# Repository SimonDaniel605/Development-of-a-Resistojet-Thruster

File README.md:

# Development of a Resistojet Thruster
This repository contains the design, modelling, simulation, and development of a low-power electrothermal resistojet propulsion system for nanosatellite station-keeping and orbital manoeuvring.

The project forms part of an MEng (Electronic Engineering) research project at Stellenbosch University and focuses on developing a compact, efficient, and manufacturable propulsion system capable of providing precise orbital manoeuvring for future small satellite missions.

The work includes analytical modelling, CFD validation, hardware development, electronics, embedded software, and experimental test infrastructure.

## Author
**Simon Daniel**  
MEng Candidate  
Electronic Systems Laboratory (ESL)  
Department of Electrical and Electronic Engineering  
Stellenbosch University

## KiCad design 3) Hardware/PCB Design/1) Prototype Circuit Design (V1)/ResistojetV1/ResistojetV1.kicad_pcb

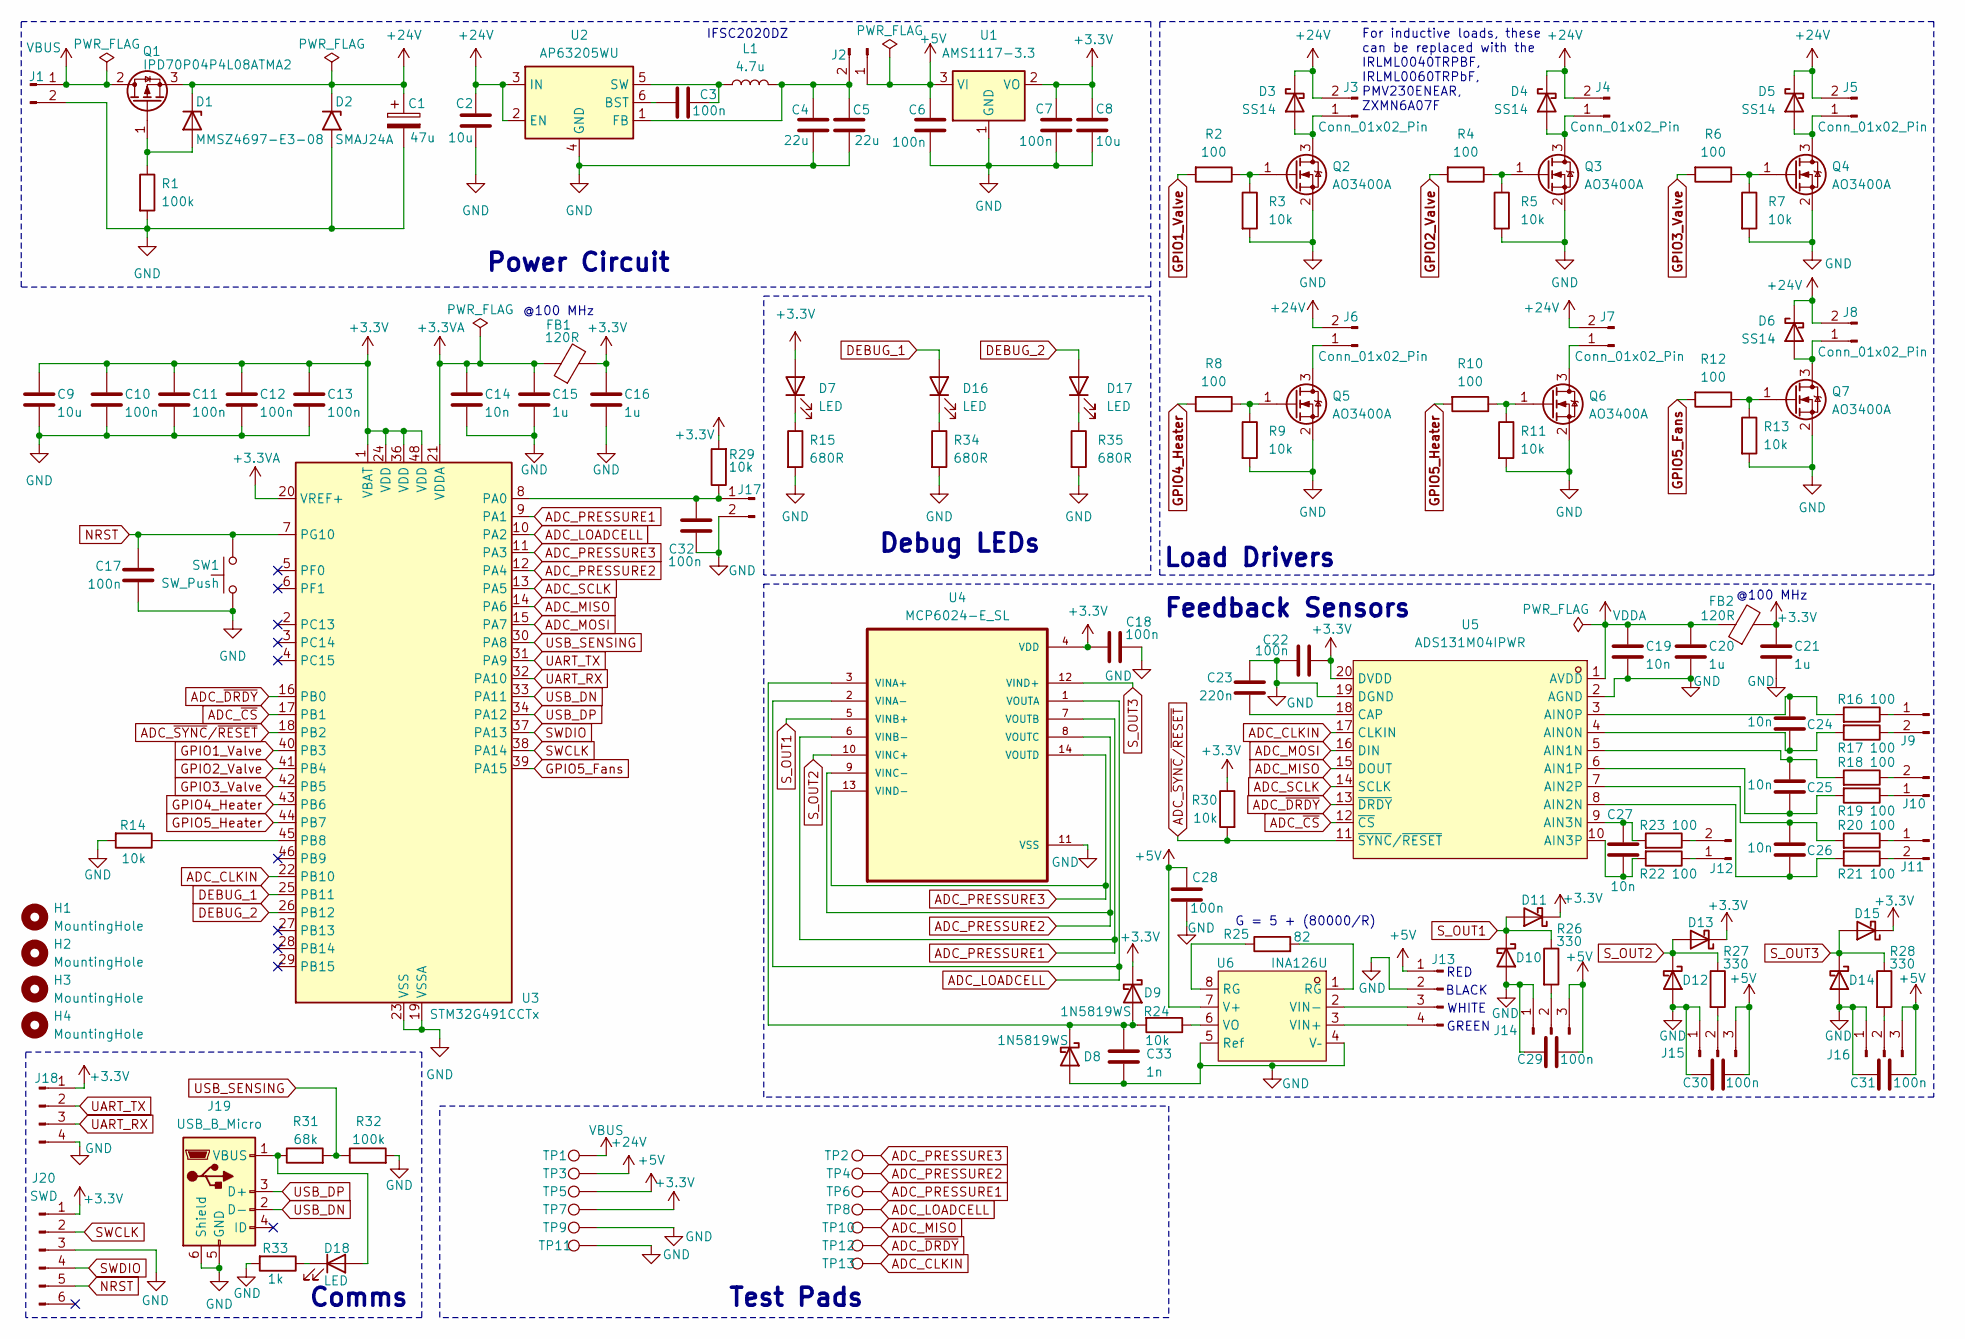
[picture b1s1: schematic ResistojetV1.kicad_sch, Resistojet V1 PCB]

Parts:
C1: 47u; CP_Elec_6.3x7.7
C2, C8, C9: 10u; C_0805_2012Metric
C3, C6, C7: 100n; C_0603_1608Metric
C4, C5: 22u; C_0805_2012Metric
C10, C11, C12, C13, C17, C18, C22, C28, C29, C30, C31, C32: 100n; C_0402_1005Metric
C14, C19, C24, C25, C26, C27: 10n; C_0402_1005Metric
C15, C16, C20, C21: 1u; C_0603_1608Metric
C23: 220n; C_0603_1608Metric
C33: 1n; C_0603_1608Metric
D1: MMSZ4697-E3-08; D_SOD-123
D2: SMAJ24A; D_SMA
D3, D4, D5, D6: SS14; D_SMA
D7, D16, D17, D18: LED; LED_0603_1608Metric
D8, D9, D10, D11, D12, D13, D14, D15: 1N5819WS; D_SOD-323
FB1, FB2: 120R; L_0603_1608Metric
H1, H2, H3, H4: MountingHole; MountingHole_3.2mm_M3
J1, J6, J7: Conn_01x02_Pin; JST_VH_B2P-VH_1x02_P3.96mm_Vertical
J2: Conn_01x02_Pin; PinHeader_1x02_P2.54mm_Vertical
J3, J4, J5, J8, J9, J10, J11, J12, J17: Conn_01x02_Pin; JST_PH_B2B-PH-K_1x02_P2.00mm_Vertical
J13, J18: Conn_01x04_Pin; JST_PH_B4B-PH-K_1x04_P2.00mm_Vertical
J14, J15, J16: Conn_01x03_Pin; JST_PH_B3B-PH-K_1x03_P2.00mm_Vertical
J19: USB_B_Micro; USB_Micro-B_Molex-105017-0001
J20: SWD; JST_PH_B6B-PH-K_1x06_P2.00mm_Vertical
L1: 4.7u; L_APV_ANR5040
Q1: IPD70P04P4L08ATMA2; TO-252-3_TabPin2
Q2, Q3, Q4, Q5, Q6, Q7: AO3400A; SOT-23
R1, R32: 100k; R_0603_1608Metric
R2, R4, R6, R8, R10, R12, R16, R17, R18, R19, R20, R21, R22, R23: 100; R_0603_1608Metric
R3, R5, R7, R9, R11, R13, R14, R24, R29, R30: 10k; R_0603_1608Metric
R15, R34, R35: 680R; R_0603_1608Metric
R25: 82; R_0603_1608Metric
R26, R27, R28: 330; R_0603_1608Metric
R31: 68k; R_0603_1608Metric
R33: 1k; R_0603_1608Metric
SW1: SW_Push; SW-SMD_L3.9-W3.0-P4.45
TP1, TP2, TP3, TP4, TP5, TP6, TP7, TP8, TP9, TP10, TP11, TP12, TP13: TestPoint; TestPoint_Pad_D1.0mm
U1: AMS1117-3.3; SOT-223-3_TabPin2
U2: AP63205WU; TSOT-23-6
U3: STM32G491CCTx; LQFP-48_7x7mm_P0.5mm
U4: MCP6024-E_SL; SOIC127P600X175-14N
U5: ADS131M04IPWR; TSSOP-20_L6.5-W4.4-P0.65-LS6.4-BL; MPN ADS131M04IPWR; LCSC Part C2862562
U6: INA126U; SOIC-8_L4.9-W3.9-P1.27-LS6.0-BL; MPN INA126U; LCSC Part C1346079

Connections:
+3.3V: C7.2, C8.2, C9.1, C10.1, C11.1, C12.1, C13.1, C16.1, C18.1, C21.1, C22.2, D7.2 (A), D9.1 (K), D11.1 (K), D13.1 (K), D15.1 (K), FB1.2, FB2.2, J18.1, J20.1, R29.2, R30.1, TP7.1, U1.2 (VO), U3.1 (VBAT), U3.24 (VDD), U3.36 (VDD), U3.48 (VDD), U4.4 (VDD), U5.20 (DVDD)
+3.3VA: C14.1, C15.1, FB1.1, U3.20 (VREF+), U3.21 (VDDA)
+5V: C6.1, C28.1, C29.1, C30.1, C31.1, J2.1, J13.1, J14.3, J15.3, J16.3, TP5.1, U1.3 (VI), U6.7 (V+)
+24V: C1.1, C2.1, D1.1 (K), D2.1 (A1), D3.1 (K), D4.1 (K), D5.1 (K), D6.1 (K), J3.2, J4.2, J5.2, J6.2, J7.2, J8.2, Q1.3 (S), TP3.1, U2.2 (EN), U2.3 (IN)
ADC_CLKIN: TP13.1, U3.22 (PB10), U5.17 (CLKIN)
ADC_LOADCELL: TP8.1, U3.10 (PA2), U4.1 (VOUTA), U4.2 (VINA-)
ADC_MISO: TP10.1, U3.14 (PA6), U5.15 (DOUT)
ADC_MOSI: U3.15 (PA7), U5.16 (DIN)
ADC_PRESSURE1: TP6.1, U3.9 (PA1), U4.6 (VINB-), U4.7 (VOUTB)
ADC_PRESSURE2: TP4.1, U3.12 (PA4), U4.8 (VOUTC), U4.9 (VINC-)
ADC_PRESSURE3: TP2.1, U3.11 (PA3), U4.13 (VIND-), U4.14 (VOUTD)
ADC_SCLK: U3.13 (PA5), U5.14 (SCLK)
ADC_~CS: U3.17 (PB1), U5.12 (~CS)
ADC_~DRDY: TP12.1, U3.16 (PB0), U5.13 (~DRDY)
ADC_~SYNC/~RESET: R30.2, U3.18 (PB2), U5.11 (~SYNC/~RESET)
DEBUG_1: D16.2 (A), U3.25 (PB11)
DEBUG_2: D17.2 (A), U3.26 (PB12)
GND: C1.2, C2.2, C4.2, C5.2, C6.2, C7.1, C8.1, C9.2, C10.2, C11.2, C12.2, C13.2, C14.2, C15.2, C16.2, C17.2, C18.2, C19.2, C20.2, C21.2, C22.1, C23.1, C28.2, C29.2, C30.2, C31.2, C32.1, C33.2, D2.2 (A2), D8.2 (A), D10.2 (A), D12.2 (A), D14.2 (A), J1.2, J13.2, J14.1, J15.1, J16.1, J17.2, J18.4, J19.5 (GND), J19.6 (Shield), J20.3, Q2.2 (S), Q3.2 (S), Q4.2 (S), Q5.2 (S), Q6.2 (S), Q7.2 (S), R1.2, R3.2, R5.2, R7.2, R9.2, R11.2, R13.2, R14.2, R15.2, R32.2, R33.2, R34.2, R35.2, SW1.2, TP9.1, TP11.1, U1.1 (GND), U2.4 (GND), U3.19 (VSSA), U3.23 (VSS), U3.35 (VSS), U3.47 (VSS), U4.11 (VSS), U5.2 (AGND), U5.19 (DGND), U6.4 (V–), U6.5 (Ref)
GPIO1_Valve: R2.2, U3.40 (PB3)
GPIO2_Valve: R4.2, U3.41 (PB4)
GPIO3_Valve: R6.2, U3.42 (PB5)
GPIO4_Heater: R8.2, U3.43 (PB6)
GPIO5_Fans: R12.2, U3.39 (PA15)
GPIO5_Heater: R10.2, U3.44 (PB7)
NRST: C17.1, J20.5, SW1.1, U3.7 (PG10)
unnamed: D1.2 (A), Q1.1 (G), R1.1
unnamed: D3.2 (A), J3.1, Q2.3 (D)
unnamed: D4.2 (A), J4.1, Q3.3 (D)
unnamed: D5.2 (A), J5.1, Q4.3 (D)
unnamed: D6.2 (A), J8.1, Q7.3 (D)
unnamed: D7.1 (K), R15.1
unnamed: C33.1, D8.1 (K), D9.2 (A), R24.2, U4.3 (VINA+)
unnamed: D16.1 (K), R34.1
unnamed: D17.1 (K), R35.1
unnamed: D18.2 (A), J19.1 (VBUS), R31.1
unnamed: D18.1 (K), R33.1
unnamed: C4.1, C5.1, J2.2, L1.2, U2.1 (FB)
unnamed: J6.1, Q5.3 (D)
unnamed: J7.1, Q6.3 (D)
unnamed: J9.1, R16.1
unnamed: J9.2, R17.1
unnamed: J10.1, R19.1
unnamed: J10.2, R18.1
unnamed: J11.1, R20.1
unnamed: J11.2, R21.1
unnamed: J12.1, R22.1
unnamed: J12.2, R23.1
unnamed: J13.3, U6.2 (VIN-)
unnamed: J13.4, U6.3 (VIN+)
unnamed: J14.2, R26.2
unnamed: J15.2, R27.2
unnamed: J16.2, R28.2
unnamed: C32.2, J17.1, R29.1, U3.8 (PA0)
unnamed: Q2.1 (G), R2.1, R3.1
unnamed: Q3.1 (G), R4.1, R5.1
unnamed: Q4.1 (G), R6.1, R7.1
unnamed: Q5.1 (G), R8.1, R9.1
unnamed: Q6.1 (G), R10.1, R11.1
unnamed: Q7.1 (G), R12.1, R13.1
unnamed: R25.1, U6.8 (RG)
unnamed: R25.2, U6.1 (RG)
unnamed: C3.1, U2.6 (BST)
unnamed: C3.2, L1.1, U2.5 (SW)
unnamed: R14.1, U3.45 (PB8)
unnamed: C24.2, R17.2, U5.4 (AIN0N)
unnamed: C24.1, R16.2, U5.3 (AIN0P)
unnamed: C25.1, R18.2, U5.5 (AIN1N)
unnamed: C25.2, R19.2, U5.6 (AIN1P)
unnamed: C26.2, R21.2, U5.8 (AIN2N)
unnamed: C26.1, R20.2, U5.7 (AIN2P)
unnamed: C27.2, R23.2, U5.9 (AIN3N)
unnamed: C27.1, R22.2, U5.10 (AIN3P)
unnamed: C23.2, U5.18 (CAP)
unnamed: R24.1, U6.6 (VO)
SWCLK: J20.2, U3.38 (PA14)
SWDIO: J20.4, U3.37 (PA13)
S_OUT1: D10.1 (K), D11.2 (A), R26.1, U4.5 (VINB+)
S_OUT2: D12.1 (K), D13.2 (A), R27.1, U4.10 (VINC+)
S_OUT3: D14.1 (K), D15.2 (A), R28.1, U4.12 (VIND+)
UART_RX: J18.3, U3.32 (PA10)
UART_TX: J18.2, U3.31 (PA9)
USB_DN: J19.2 (D-), U3.33 (PA11)
USB_DP: J19.3 (D+), U3.34 (PA12)
USB_SENSING: R31.2, R32.1, U3.30 (PA8)
VBUS: J1.1, Q1.2 (D), TP1.1
VDDA: C19.1, C20.1, FB2.1, U5.1 (AVDD)

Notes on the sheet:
WHITE
G = 5 + (80000/R)
Comms
@100 MHz
Test Pads
Debug LEDs
Feedback Sensors
RED
Power Circuit
IFSC2020DZ
Load Drivers
GREEN
For inductive loads, these can be replaced with the IRLML0040TRPBF, IRLML0060TRPbF, PMV230ENEAR, ZXMN6A07F
BLACK

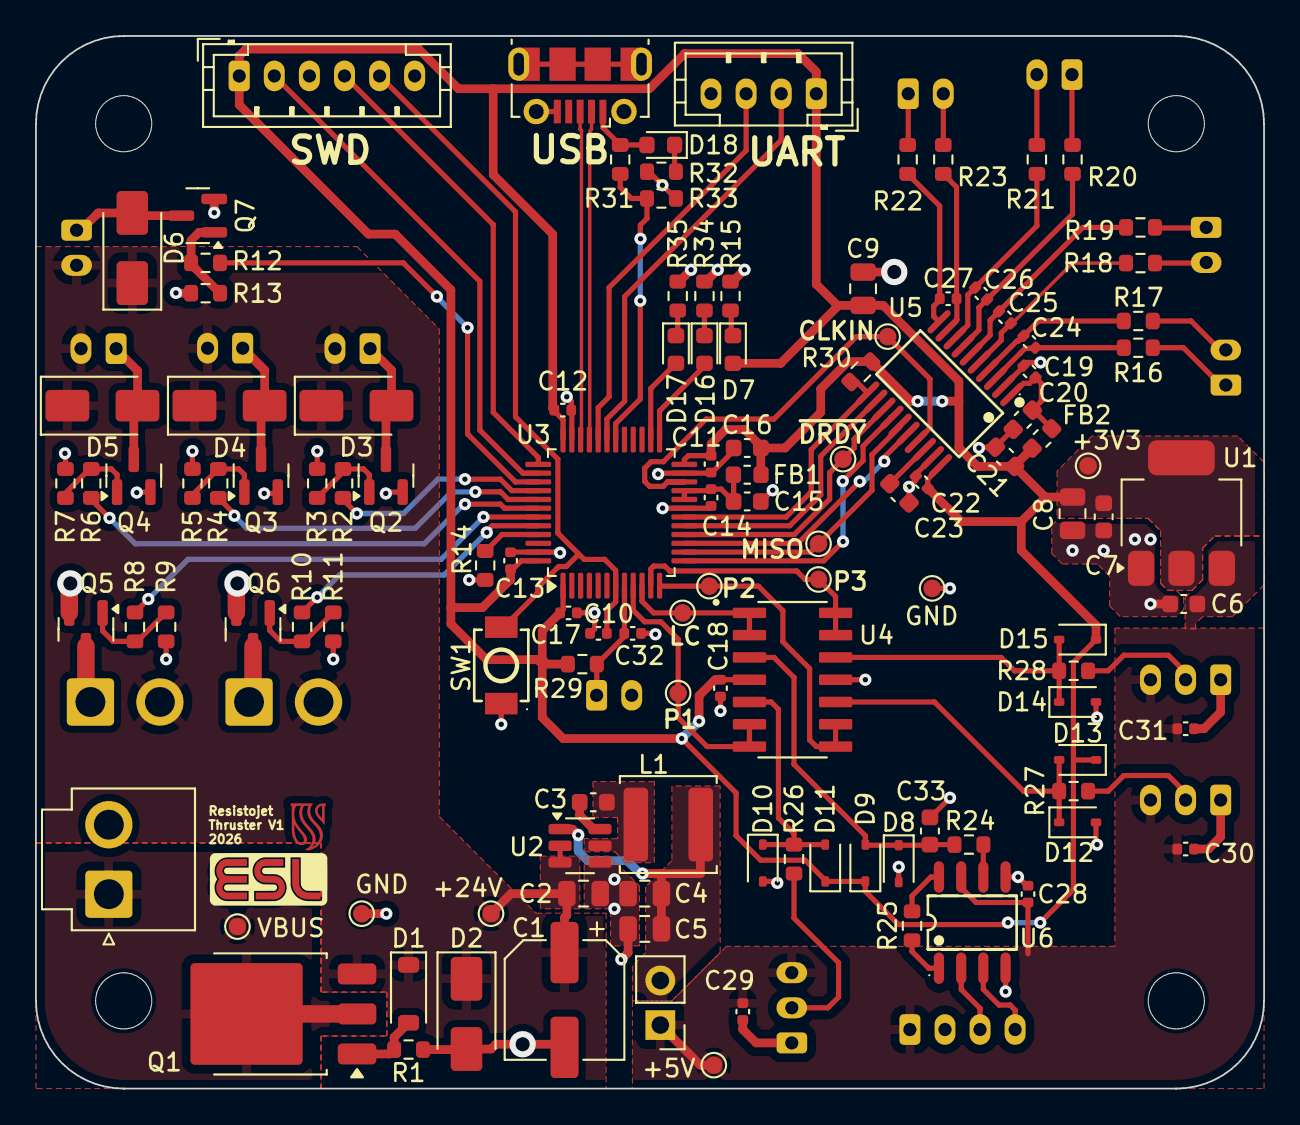
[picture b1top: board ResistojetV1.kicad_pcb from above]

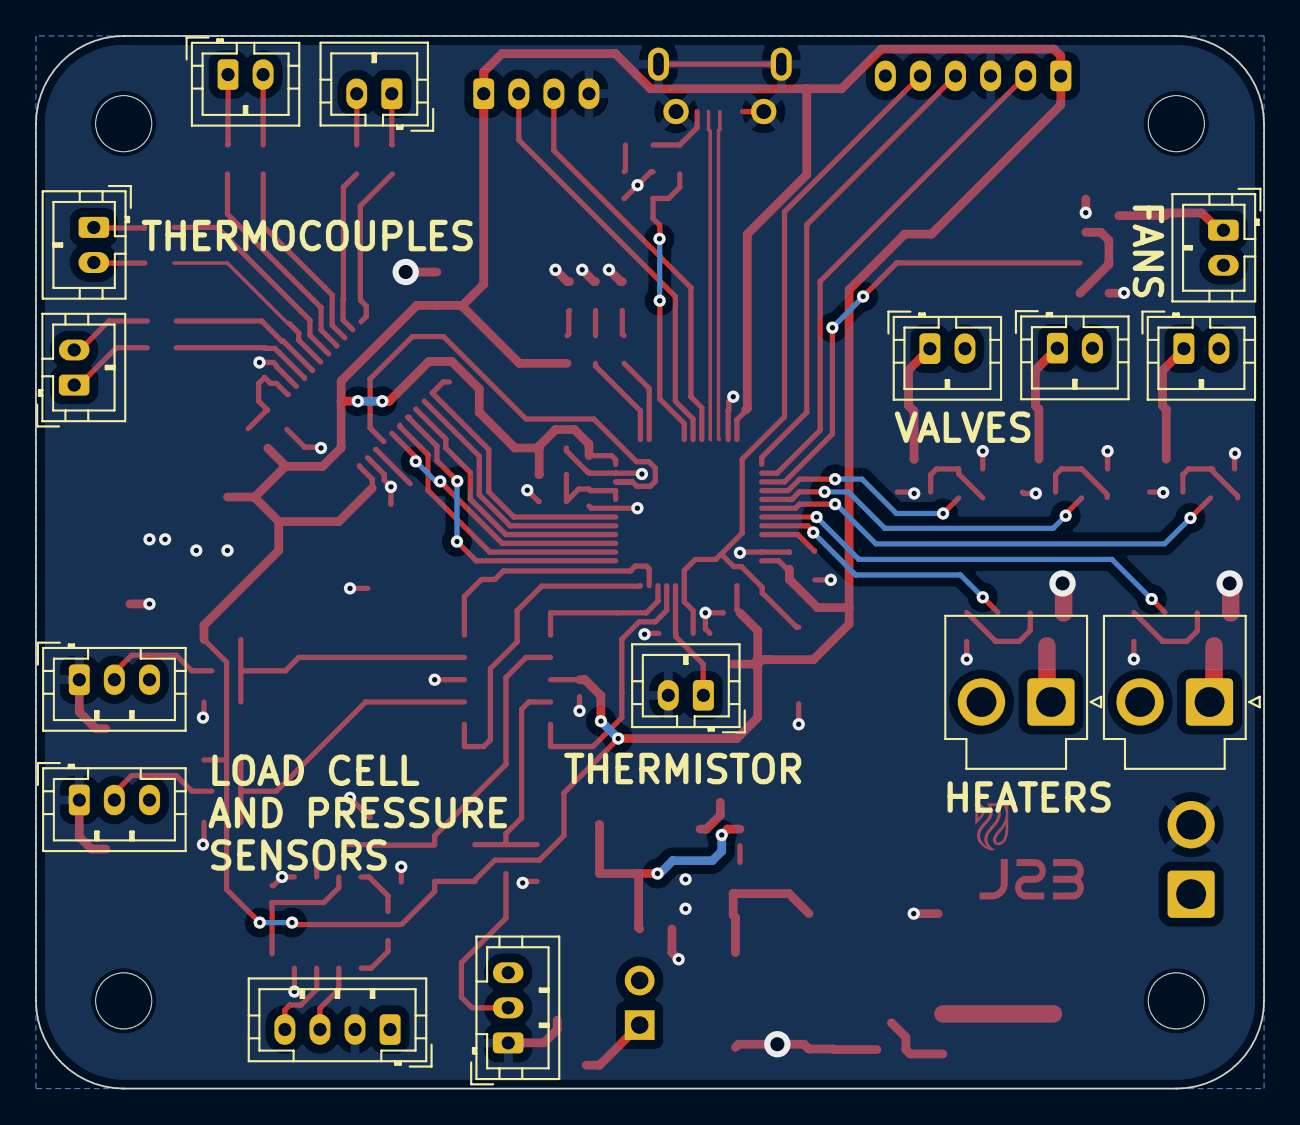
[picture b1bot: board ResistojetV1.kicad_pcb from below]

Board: 2 copper layers, 70.0 x 60.0 mm, 142 parts (15 on the bottom side), 86 nets.

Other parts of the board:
ESL_LOGO: LOGO
SU_LOGO: LOGO

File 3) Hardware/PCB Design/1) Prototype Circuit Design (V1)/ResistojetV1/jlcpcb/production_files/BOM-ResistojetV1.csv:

Comment,Designator,Footprint,LCSC,Quantity
100,"R10,R12,R16,R17,R18,R19,R2,R20,R21,R22,R23,R4,R6,R8",R_0603_1608Metric,C22775,14
100k,"R1,R32",R_0603_1608Metric,C25803,2
100n,"C3,C6,C7",C_0603_1608Metric,C14663,3
100n,"C10,C11,C12,C13,C17,C18,C22,C28,C29,C30,C31,C32",C_0402_1005Metric,C1525,12
10k,"R11,R13,R14,R24,R29,R3,R30,R5,R7,R9",R_0603_1608Metric,C25804,10
10n,"C14,C19,C24,C25,C26,C27",C_0402_1005Metric,C15195,6
10u,"C8,C9",C_0805_2012Metric,C15850,2
10u,C2,C_0805_2012Metric,C440198,1
120R,"FB1,FB2",L_0603_1608Metric,C14709,2
1N5819WS,"D10,D11,D12,D13,D14,D15,D8,D9",D_SOD-323,C191023,8
1k,R33,R_0603_1608Metric,C21190,1
1n,C33,C_0603_1608Metric,C1588,1
1u,"C15,C16,C20,C21",C_0603_1608Metric,C15849,4
220n,C23,C_0603_1608Metric,C21120,1
22u,"C4,C5",C_0805_2012Metric,C45783,2
330,"R26,R27,R28",R_0603_1608Metric,C23138,3
680R,"R15,R34,R35",R_0603_1608Metric,C23228,3
68k,R31,R_0603_1608Metric,C23231,1
AMS1117-3.3,U1,SOT-223-3_TabPin2,C6186,1
AO3400A,"Q2,Q3,Q4,Q5,Q6,Q7",SOT-23,C20917,6
AP63205WU,U2,TSOT-23-6,C2071056,1
LED,"D16,D17",LED_0603_1608Metric,C2286,2
LED,"D18,D7",LED_0603_1608Metric,C2290,2
SS14,"D3,D4,D5,D6",D_SMA,C2480,4
SW_Push,SW1,SW-SMD_L3.9-W3.0-P4.45,C720477,1

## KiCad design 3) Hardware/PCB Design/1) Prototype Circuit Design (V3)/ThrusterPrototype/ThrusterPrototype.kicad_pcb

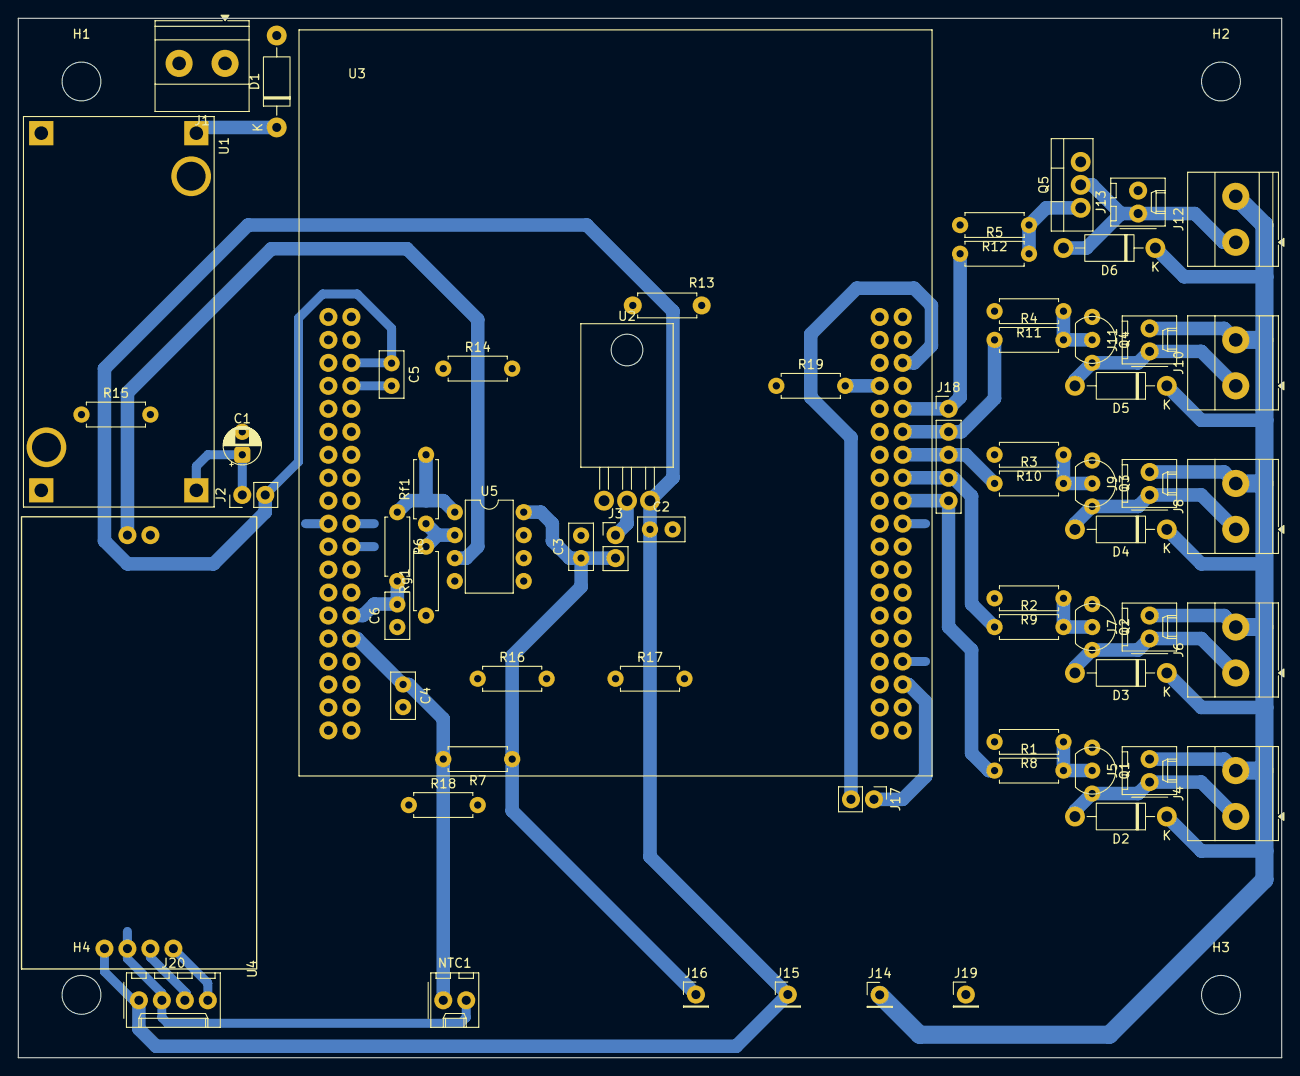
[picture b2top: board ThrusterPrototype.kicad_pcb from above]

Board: 2 copper layers, 139.7 x 114.9 mm, 68 parts (0 on the bottom side), 31 nets.

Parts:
C1: 10u; CP_Radial_D4.0mm_P2.00mm
C2, C3, C4, C5: 100n; C_Disc_D5.0mm_W2.5mm_P2.50mm
C6: Clp; C_Disc_D5.0mm_W2.5mm_P2.50mm
D1, D2, D3, D4, D5, D6: 1N4007; D_DO-41_SOD81_P10.16mm_Horizontal
H1, H2, H3, H4: MountingHole; MountingHole_4.3mm_M4
J1, J4, J6, J8, J10, J12: Screw_Terminal_01x02; TerminalBlock_Phoenix_MKDS-1,5-2-5.08_1x02_P5.08mm_Horizont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
J2, J3, J17: Conn_01x02_Pin; PinHeader_1x02_P2.54mm_Vertical
J5, J7, J9, J11, J13: Conn_01x02_Pin; Molex_KK-254_AE-6410-02A_1x02_P2.54mm_Vertical
J14, J15, J16, J19: Conn_01x01_Pin; PinHeader_1x01_P2.54mm_Vertical
J18: Conn_01x05_Pin; PinHeader_1x05_P2.54mm_Vertical
J20: Conn_01x04_Pin; Molex_KK-254_AE-6410-04A_1x04_P2.54mm_Vertical
NTC1: 10k; Molex_KK-254_AE-6410-02A_1x02_P2.54mm_Vertical
Q1, Q2, Q3, Q4: 2N7000; TO-92_Inline
Q5: IRLZ44N; TO-220-3_Vertical
R1, R2, R3, R4, R5: 330; R_Axial_DIN0207_L6.3mm_D2.5mm_P7.62mm_Horizontal
R6: Rlp; R_Axial_DIN0207_L6.3mm_D2.5mm_P7.62mm_Horizontal
R7: 10k; R_Axial_DIN0207_L6.3mm_D2.5mm_P7.62mm_Horizontal
R8, R9, R10, R11, R12: 100k; R_Axial_DIN0207_L6.3mm_D2.5mm_P7.62mm_Horizontal
R13, R14, R15, R16, R17, R18, R19: 0; R_Axial_DIN0207_L6.3mm_D2.5mm_P7.62mm_Horizontal
Rf1: Rlp; R_Axial_DIN0207_L6.3mm_D2.5mm_P7.62mm_Horizontal
Rg1: Rlp; R_Axial_DIN0207_L6.3mm_D2.5mm_P7.62mm_Horizontal
U1: MC00100; CONV_MC00100
U2: LD1117V33; TO-220-3_Horizontal_TabDown
U3: NUCLEO-G0B1RE; MODULE_NUCLEO-G0B1RE
U4: Untitled
U5: MCP602; DIP-8_W7.62mm

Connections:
+3.3V: C3.1, J3.2, J16.1, R7.1, U5.8 (V+)
+5V: C2.1, C5.1, J2.2, J15.1, J20.1, U2.3 (VI), U3.CN7_6, U4.1 (VIN)
+24V: D1.2 (A), D2.1 (K), D3.1 (K), D4.1 (K), D5.1 (K), D6.1 (K), J1.1, J4.2, J5.2, J6.2, J7.2, J8.2, J9.2, J10.2, J11.2, J12.2, J13.2, J14.1
GND: C1.2, C2.2, C3.2, C4.2, C5.2, C6.1, J1.2, J19.1, J20.2, NTC1.2, Q1.1 (S), Q2.1 (S), Q3.1 (S), Q4.1 (S), Q5.3 (S), R8.2, R9.2, R10.2, R11.2, R12.2, R13.1, R13.2, R14.1, R14.2, R15.1, R15.2, R16.1, R16.2, R17.1, R17.2, R18.1, R18.2, R19.1, R19.2, Rg1.1, U1.IN-, U1.MH1 (MOUTING), U1.MH2 (MOUTING), U1.OUT-, U2.1 (GND), U3.CN7_8, U3.CN7_19, U3.CN7_20, U3.CN7_22, U3.CN10_7, U3.CN10_20, U3.CN10_32, U4.2 (GND), U4.6 (GND), U5.4 (V-)
unnamed: C4.1, NTC1.1, R7.2, U3.CN7_30 (PA1)
unnamed: C6.2, R6.2, U3.CN7_28 (PA0)
unnamed: D1.1 (K), U1.IN+
unnamed: D2.2 (A), J4.1, J5.1, Q1.3 (D)
unnamed: D3.2 (A), J6.1, J7.1, Q2.3 (D)
unnamed: D4.2 (A), J8.1, J9.1, Q3.3 (D)
unnamed: D5.2 (A), J10.1, J11.1, Q4.3 (D)
unnamed: D6.2 (A), J12.1, J13.1, Q5.2 (D)
unnamed: C1.1, J2.1, U1.OUT+
unnamed: J3.1, U2.2 (VO)
unnamed: J17.1, U3.CN10_34 (PA2)
unnamed: J17.2, U3.CN10_6 (PA3)
unnamed: J18.1, R5.1, U3.CN10_10 (PD6)
unnamed: J18.2, R4.1, U3.CN10_12 (PA12)
unnamed: J18.3, R3.1, U3.CN10_14 (PA11)
unnamed: J18.4, R2.1, U3.CN10_16 (PC1)
unnamed: J18.5, R1.1, U3.CN10_18 (PC0)
unnamed: J20.3, U4.3 (S-)
unnamed: J20.4, U4.4 (S+)
unnamed: Q1.2 (G), R1.2, R8.1
unnamed: Q2.2 (G), R2.2, R9.1
unnamed: Q3.2 (G), R3.2, R10.1
unnamed: Q4.2 (G), R4.2, R11.1
unnamed: Q5.1 (G), R5.2, R12.1
unnamed: R6.1, Rf1.2, U5.1
unnamed: U4.5 (VOUT), U5.3 (+)
unnamed: Rf1.1, Rg1.2, U5.2 (-)

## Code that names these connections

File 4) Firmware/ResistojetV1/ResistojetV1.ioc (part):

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Mcu.Name=STM32G491C(C-E)Tx
Mcu.Package=LQFP48
Mcu.UserName=STM32G491CCTx
PA0.Mode=IN1-Single-Ended
PA0.Signal=ADC1_IN1
PA1.Mode=IN2-Single-Ended
PA1.Signal=ADC1_IN2
PA11.Mode=Device
PA11.Signal=USB_DM
PA12.Mode=Device
PA12.Signal=USB_DP
PA13.Mode=Serial_Wire
PA13.Signal=SYS_JTMS-SWDIO
PA14.Mode=Serial_Wire
PA14.Signal=SYS_JTCK-SWCLK
PA15.Signal=GPIO_Output
PA2.Mode=IN3-Single-Ended
PA2.Signal=ADC1_IN3
PA3.Mode=IN4-Single-Ended
PA3.Signal=ADC1_IN4
PA4.Mode=IN17-Single-Ended
PA4.Signal=ADC2_IN17
PA5.Mode=Full_Duplex_Master
PA5.Signal=SPI1_SCK
PA6.Mode=Full_Duplex_Master
PA6.Signal=SPI1_MISO
PA7.Mode=Full_Duplex_Master
PA7.Signal=SPI1_MOSI
PA8.Signal=GPXTI8
PB0.Signal=GPXTI0
PB1.GPIOParameters=PinState
PB1.PinState=GPIO_PIN_SET
PB1.Signal=GPIO_Output
PB10.Signal=S_TIM2_CH3
PB11.Signal=GPIO_Output
PB12.Signal=GPIO_Output
PB2.GPIOParameters=PinState
PB2.PinState=GPIO_PIN_SET
PB2.Signal=GPIO_Output
PB3.Signal=GPIO_Output
PB4.Signal=GPIO_Output
PB5.Signal=GPIO_Output
PB6.Signal=S_TIM4_CH1
PB7.Signal=S_TIM4_CH2
RCC.HSE_VALUE=8000000
RCC.SYSCLKFreq_VALUE=128000000
RCC.SYSCLKSource=RCC_SYSCLKSOURCE_PLLCLK
board=custom

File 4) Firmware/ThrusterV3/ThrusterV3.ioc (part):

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Mcu.Name=STM32G0B1R(B-C-E)Tx
Mcu.Package=LQFP64
Mcu.UserName=STM32G0B1RETx
PA0.Signal=SharedAnalog_PA0
PA1.Signal=SharedAnalog_PA1
PA12\ [PA10].Signal=GPIO_Output
PA13.GPIOParameters=GPIO_Label
PA13.GPIO_Label=TMS
PA13.Mode=Serial_Wire
PA13.Signal=SYS_SWDIO
PA14-BOOT0.GPIOParameters=GPIO_Label
PA14-BOOT0.GPIO_Label=TCK
PA14-BOOT0.Mode=Serial_Wire
PA14-BOOT0.Signal=SYS_SWCLK
PA2.GPIOParameters=GPIO_Label
PA2.GPIO_Label=USART2_TX [STLK_TX]
PA2.Mode=Asynchronous
PA2.Signal=USART2_TX
PA3.GPIOParameters=GPIO_Label
PA3.GPIO_Label=USART2_RX [STLK_RX]
PA3.Mode=Asynchronous
PA3.Signal=USART2_RX
PC13.GPIOParameters=GPIO_Label
PC13.GPIO_Label=B1 [blue push button]
PC13.Signal=GPXTI13
PC14-OSC32_IN\ (PC14).Mode=LSE-External-Oscillator
PC14-OSC32_IN\ (PC14).Signal=RCC_OSC32_IN
PC15-OSC32_OUT\ (PC15).Mode=LSE-External-Oscillator
PC15-OSC32_OUT\ (PC15).Signal=RCC_OSC32_OUT
PD6.Signal=GPIO_Output
PF0-OSC_IN\ (PF0).GPIOParameters=GPIO_Label
PF0-OSC_IN\ (PF0).GPIO_Label=MCO
PF0-OSC_IN\ (PF0).Mode=HSE-External-Clock-Source
PF0-OSC_IN\ (PF0).Signal=RCC_OSC_IN
RCC.HSE_VALUE=8000000
RCC.SYSCLKFreq_VALUE=64000000
RCC.SYSCLKSource=RCC_SYSCLKSOURCE_PLLCLK
board=NUCLEO-G0B1RE
boardIOC=true
